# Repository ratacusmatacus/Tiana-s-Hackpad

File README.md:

# Tiana-s-Hackpad

- 1x Seeed XIAO RP2040
- 12x Through-hole 1N4148 Diodes
- 12x MX-Style switches 
- 1x EC11 Rotary encoders
- 1x 0.91 inch OLED displays
- 12x Blank DSA keycaps
- 4x M3x16mm screws
- 4x M3x5mx4mm heatset inserts

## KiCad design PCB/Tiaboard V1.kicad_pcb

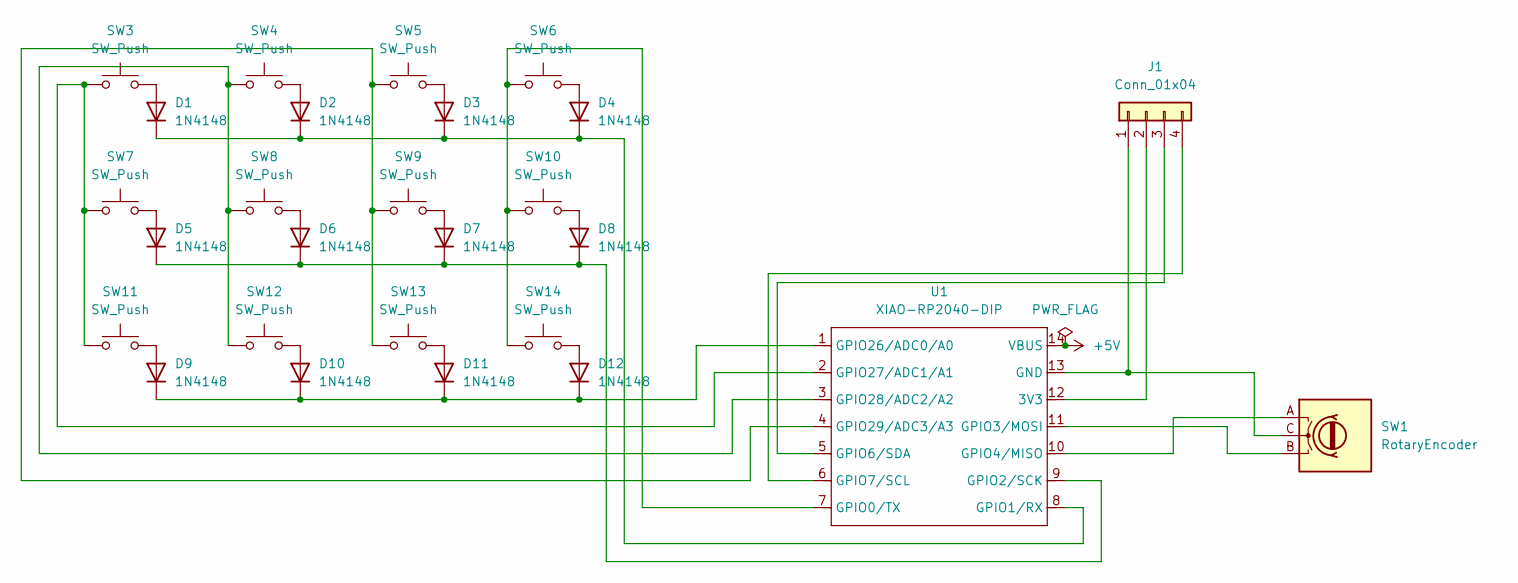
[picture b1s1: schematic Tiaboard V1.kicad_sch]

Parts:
D1, D2, D3, D4, D5, D6, D7, D8, D9, D10, D11, D12: 1N4148; D_DO-35_SOD27_P7.62mm_Horizontal
J1: Conn_01x04; SSD1306-0.91-OLED-4pin-128x32
SW1: RotaryEncoder; RotaryEncoder_Alps_EC11E-Switch_Vertical_H20mm
SW3, SW4, SW5, SW6, SW7, SW8, SW9, SW10, SW11, SW12, SW13, SW14: SW_Push; SW_Cherry_MX_1.00u_PCB
U1: XIAO-RP2040-DIP

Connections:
+5V: U1.14 (VBUS)
unnamed: D1.2 (A), SW3.2
unnamed: D1.1 (K), D2.1 (K), D3.1 (K), D4.1 (K), U1.8 (GPIO1/RX)
unnamed: D2.2 (A), SW4.2
unnamed: D3.2 (A), SW5.2
unnamed: D4.2 (A), SW6.2
unnamed: D5.2 (A), SW7.2
unnamed: D5.1 (K), D6.1 (K), D7.1 (K), D8.1 (K), U1.9 (GPIO2/SCK)
unnamed: D6.2 (A), SW8.2
unnamed: D7.2 (A), SW9.2
unnamed: D8.2 (A), SW10.2
unnamed: D9.2 (A), SW11.2
unnamed: D10.2 (A), SW12.2
unnamed: D9.1 (K), D10.1 (K), D11.1 (K), D12.1 (K), U1.1 (GPIO26/ADC0/A0)
unnamed: D11.2 (A), SW13.2
unnamed: D12.2 (A), SW14.2
unnamed: J1.1 (GND), SW1.C, U1.13 (GND)
unnamed: J1.4 (SCL), U1.6 (GPIO7/SCL)
unnamed: J1.3 (SDA), U1.5 (GPIO6/SDA)
unnamed: J1.2 (VCC), U1.12 (3V3)
unnamed: SW6.1, SW10.1, SW14.1, U1.7 (GPIO0/TX)
unnamed: SW1.B, U1.11 (GPIO3/MOSI)
unnamed: SW1.A, U1.10 (GPIO4/MISO)
unnamed: SW3.1, SW7.1, SW11.1, U1.2 (GPIO27/ADC1/A1)
unnamed: SW4.1, SW8.1, SW12.1, U1.3 (GPIO28/ADC2/A2)
unnamed: SW5.1, SW9.1, SW13.1, U1.4 (GPIO29/ADC3/A3)

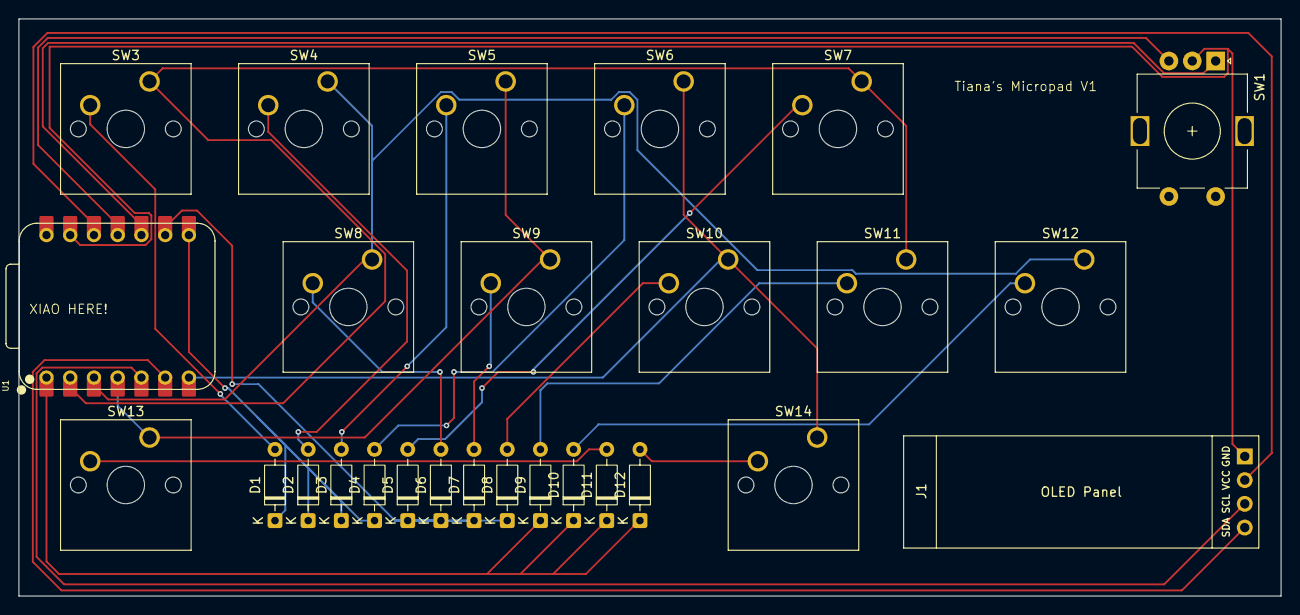
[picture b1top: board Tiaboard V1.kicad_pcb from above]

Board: 2 copper layers, 135.1 x 61.8 mm, 27 parts (0 on the bottom side), 25 nets.

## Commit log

2025-12-05 Create CAD
2025-12-05 Create PCB
2025-12-05 Create FIRMWARE
2025-12-05 Create Hackpad Acquired Instructions
2025-12-05 Rename Hackpad Acquired Instructions to Hackpad Acquired Instructions.md
